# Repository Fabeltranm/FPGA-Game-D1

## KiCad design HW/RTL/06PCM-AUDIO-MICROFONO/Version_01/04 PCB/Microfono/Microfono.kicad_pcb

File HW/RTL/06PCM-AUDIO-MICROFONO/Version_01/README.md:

# SISTEMA DE AUDIO

## Integrantes del equipo de trabajo:

### 1 Lisseth Tatiana Herrera Rosero ltherreraro@unal.edu.co

### 2 Santiago Esteban Guevara Rozo seguevarar@unal.edu.co

### 3 Michael Fabian Sierra Tarazona mfsierrat@unal.edu.co

## Descripción general del sistema: 

En el módulo de audio se pretende garantizar la grabación de una voz por un lapso aproximado de 2 segundos,  digitalizar, guardar y reproducir esta señal, se utilizaran dos grandes modulos en el cual se tienen microfono y altavoz
En el módulo del micrófono se tendrá una señal análoga con frecuencia de 1 a 5 kHz, la cual entrará a un convertidor A/D, acontinuación se procesará en un filtro pasabajos logrando una salida de 18 bits; Esta entrará a nuestra FPGA nexys4 donde se guardará por módulos en un proceso FIFO sincrónico, el sincronismo de los clocks es necesario para acoplar todas las fases de dicho proceso.
En la segunda etapa (altavoz), entra dicha informacion a un convertidor D/A (PCM) el cual también logra amplificar esta señal para poder ser reproducida.

## Descripción de la caja funcional (Modulo Microfono):
En este módulo depende del modulo divisor de frecuencia. El divisor de frecuencia es necesario para obtener los clocks de sincranización de el módulo de micrófono y de altavoz.

Este modulo tiene entradas: 
* **Data** datos provenientes del micrófono (conformado por 32 bits) de los cuales solo 18 se van a usar para la salida 
* **Enable** para inicializar (conformado por 1 bit)

Este módulo tiene salidas:
* **Clk** El clock que necesita el micrófono para modular la señal y enviarla (conformado por 1 bit)
* **ws** necesario más adelante para seleccionar derecho o izquierdo (conformado por 1 bit)
* **Dataout** datos de salida serializado (conformado por 1 bit)
* **done** para indicar que finalizó la acción (conformado por 1 bit)

Y finalmente tiene un parametro
* **Count** para contar las interacciones 

### Descripción funcional (Módulo Micrófono MEMS):
Para que el modulo de microfono este activo la frecuencia del clk debe estar ser mayor a 1MHz y tener el voltaje VDD activo, pero esto se garantiza en el divisor de frecuencia.

## Descripción de la caja funcional (Modulo Altavoz):
En este módulo tambien depende de el modulo divisor de frecuencia. 

Este modulo tiene entradas: 
* **Data** datos provenientes del micrófono ya serializados (conformado por 1 bit) 
* **Enable** para inicializar (conformado por 1 bit)

Este módulo tiene salidas:
* **Bclk** El clock que necesita el altavoz para recuperar los datos(conformado por 1 bit)
* **LRclk** necesario para seleccionar derecho o izquierdo (conformado por 1 bit)
* **Data_R** datos de salida canal derecho (conformado por 16 bit)
* **Data_L** datos de salida canal izquierdo (conformado por 16 bit)
* **done** para indicar que finalizó la acción (conformado por 1 bit)

Y finalmente tiene un parametro
* **Count** para contar las interacciones 

### Descripción funcional (Módulo Altavoz):
El LRclk tiene un delay de 1 ciclo de Bclk por lo tanto solo soporta frecuencias de 8KHz, 16KHz, 32KHz, 44.1KHz, 48KHz, 88.2KHz y 96KHz, pero esto se garantiza en el divisor de frecuencia.

## Descripción de la caja funcional (Módulo Divisor de frecuencia):
Este modulo tiene entradas: 
* **Clk** El clock que necesita realizar la divison de señal (conformado por 1 bit)
* **Reset** para reiniciar el sistema (conformado por 1 bit)

Este módulo tiene salidas:
* **Clkout** El clock que se deseaba (conformado por 1 bit)
Y finalmente tiene como parametros
* **fi** Frecuencia de entrada
* **fo** Frecuencia de salida (la que se desea obtener)
* **Count** para contar las interacciones 

### Descripción funcional (Divisor de frecuencia):

## Descripción Estructural: 

## Diagrama de Estados:

## Arquitectura del periférico:

XXXXXXXXXXXXXXXXXXXXXXXXXXXXXXXXXXXXXXXXXXXXXXXXXX

## Diagrama de bloques del periférico:

XXXXXXXXXXXXXXXXXXXXXXXXXXXXXXXXXXXXXXXXXXXXXXXXXX

## referencias:
-Datasheet Microfono mems SPH0645LM4H-B,[online] knowls, Disponible en: https://www.digikey.com/product-detail/es/knowles/SPH0645LM4H-B/423-1405-1-ND/5332432
-Datasheet Nexys 4TM FPGA Board Reference Manual,[online], Digilent Disponible en: http://store.digilentinc.com/nexys-4-artix-7-fpga-trainer-board-limited-time-see-nexys4-ddr/
-Datasheet PCM Audio MAX98357A,[online] Maxim integrated, Disponible en:http://www.alldatasheet.com/view.jsp?Searchword=Max98357a

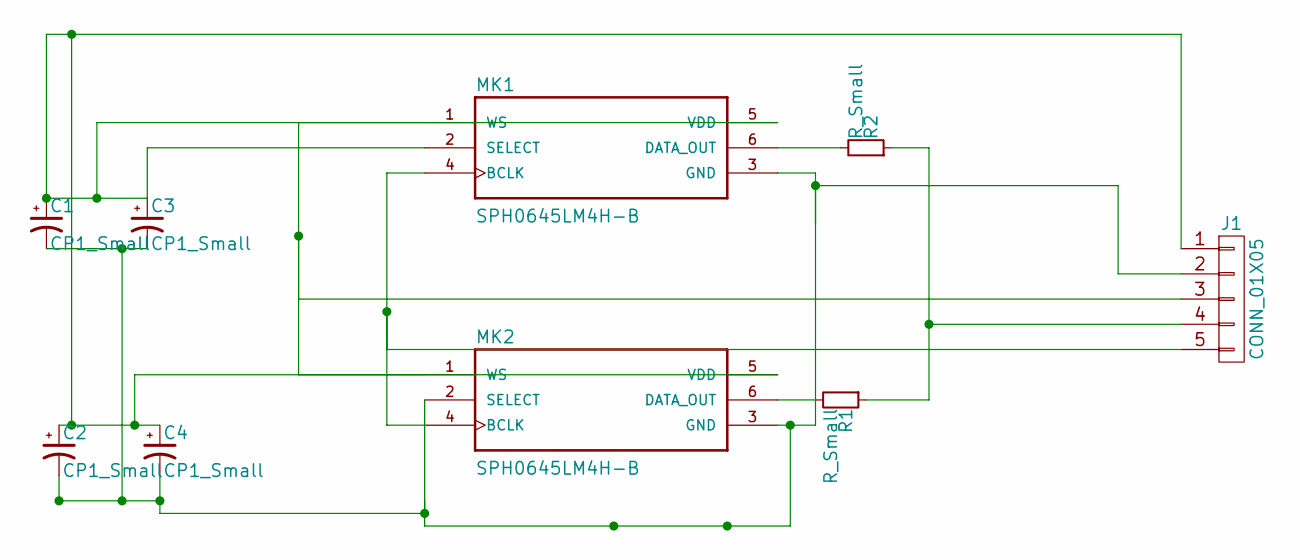
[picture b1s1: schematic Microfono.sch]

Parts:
C1, C2, C3, C4: CP1_Small; CP_Tantalum_Case-A_EIA-3216-18_Hand
J1: CONN_01X05; Pin_Header_Angled_1x05_Pitch1.00mm
MK1, MK2: SPH0645LM4H-B; MIC_SPH0645LM4H-B
R1, R2: R_Small; R_0201

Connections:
unnamed: C1.1, C2.1, C3.1, C4.1, J1.1, MK1.2 (SELECT), MK1.5 (VDD), MK2.5 (VDD)
unnamed: C1.2, C2.2, C3.2, C4.2, J1.2, MK1.3 (GND), MK2.2 (SELECT), MK2.3 (GND)
unnamed: J1.3, MK1.1 (WS), MK2.1 (WS)
unnamed: J1.4, R1.1, R2.1
unnamed: J1.5, MK1.4 (BCLK), MK2.4 (BCLK)
unnamed: MK1.6 (DATA_OUT), R2.2
unnamed: MK2.6 (DATA_OUT), R1.2

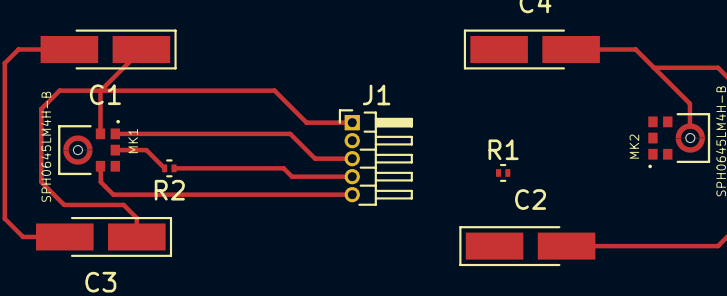
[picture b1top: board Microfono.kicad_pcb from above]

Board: 2 copper layers, 9 parts (0 on the bottom side), 7 nets.

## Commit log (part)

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2017-10-30 fifo
2017-10-31 prueba
2017-10-31 carpeta codigos
2017-10-31 data microfono
2017-11-01 micled
2017-11-03 prueba gtkw tx
2017-11-03 borrar
2017-11-03 prueba tx
2017-11-03 03-nov
2017-11-07 codigo
2017-11-07 verilog
2017-11-07 microfono
2017-11-07 prueba fifo
2017-11-08 Create Camera ov7670
2017-11-08 Create Camera
2017-11-08 carpetas
2017-11-10 Funciona!
2017-11-10 prueba 2
2017-11-12 cambios
2017-11-14 Prueba 3
2017-11-15 Prueba 4
2017-11-15 Prueba 5
2017-11-20 Transmision1
2017-11-20 carpeta
2017-11-21 Prueba 5 y prueba 6
2017-11-21 pruebas
2017-11-21 Prueba5
2017-11-21 archivo
2017-11-21 imagen
2017-11-22 Mover
2017-11-22 Reemplazar
2017-11-22 Atlys Carpeta
2017-11-22 Adicionar Carpeta
2017-11-22 Eliminar
2017-11-22 Agregar
2017-11-24 Quitar Archivo Vacio
2017-11-24 numeros
2017-11-24 Prueba4
2017-11-27 Prueba 4 y fifo
2017-11-27 Prueba 3 y periferico
2017-11-28 pruebas fifo
2017-11-28 pruebas readme
2017-11-28 Change
2017-11-28 codigo bt
2017-11-30 temp
2017-11-30 Create J1_Union_modulo
2017-11-30 Create sauriann101418-patch-1
2017-11-30 Update Makefile
2017-11-30 Create makefile
2017-11-30 Create app.fs~
2017-12-01 Create Periferico
2017-12-01 Create file
2017-12-01 periferico
2017-12-01 escribir
2017-12-01 varias cosas
2017-12-01 final
2017-12-01 modificar
2017-12-01 modificación
2017-12-01 agregar en makefile j1soc
2017-12-01 modificaar
2017-12-01 testbench
2017-12-01 Create vacio
2017-12-01 Create vacion
2017-12-01 Create a
2017-12-01 Rename Microfono_TB.v to Microfono_TB
2017-12-01 readme
